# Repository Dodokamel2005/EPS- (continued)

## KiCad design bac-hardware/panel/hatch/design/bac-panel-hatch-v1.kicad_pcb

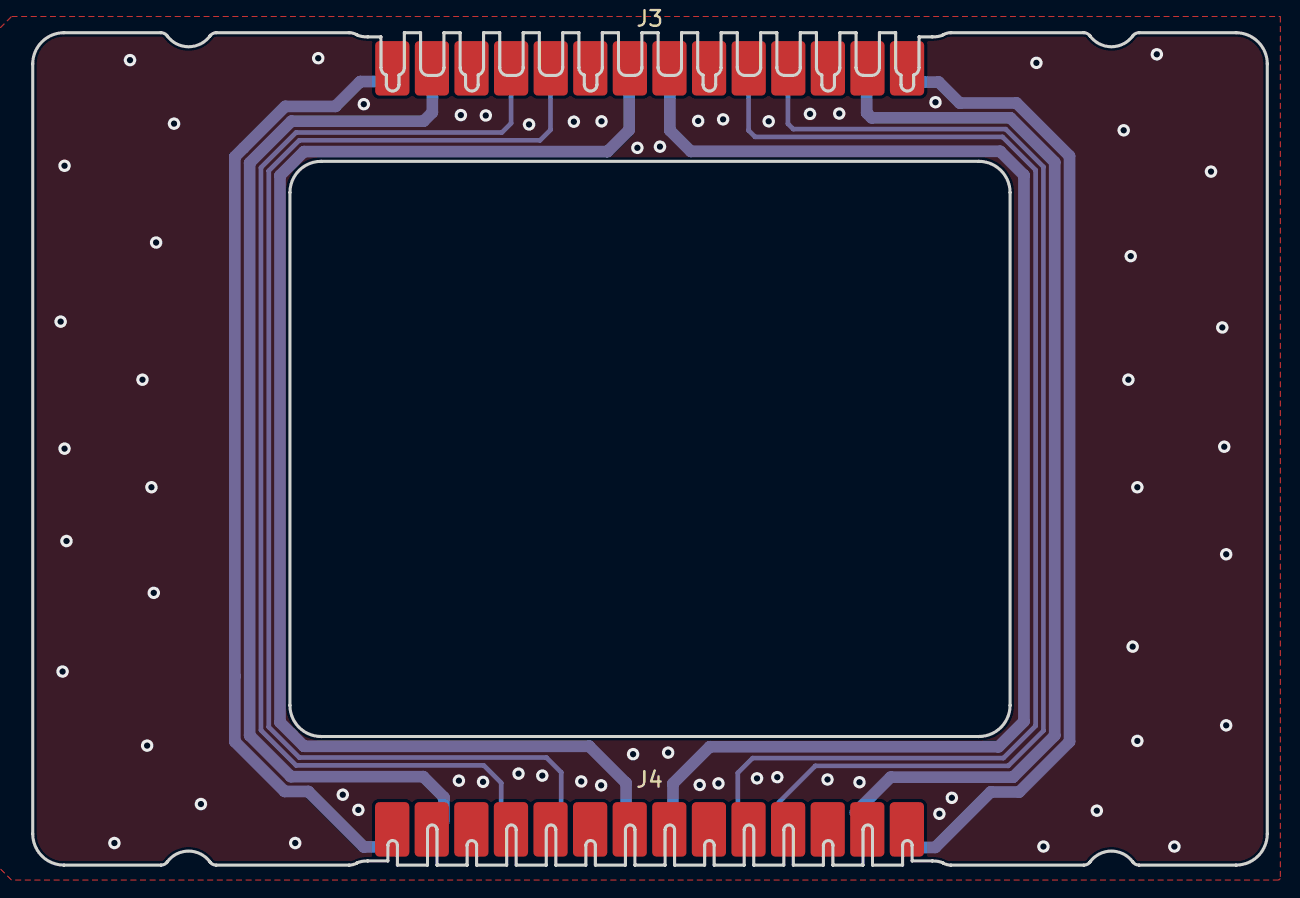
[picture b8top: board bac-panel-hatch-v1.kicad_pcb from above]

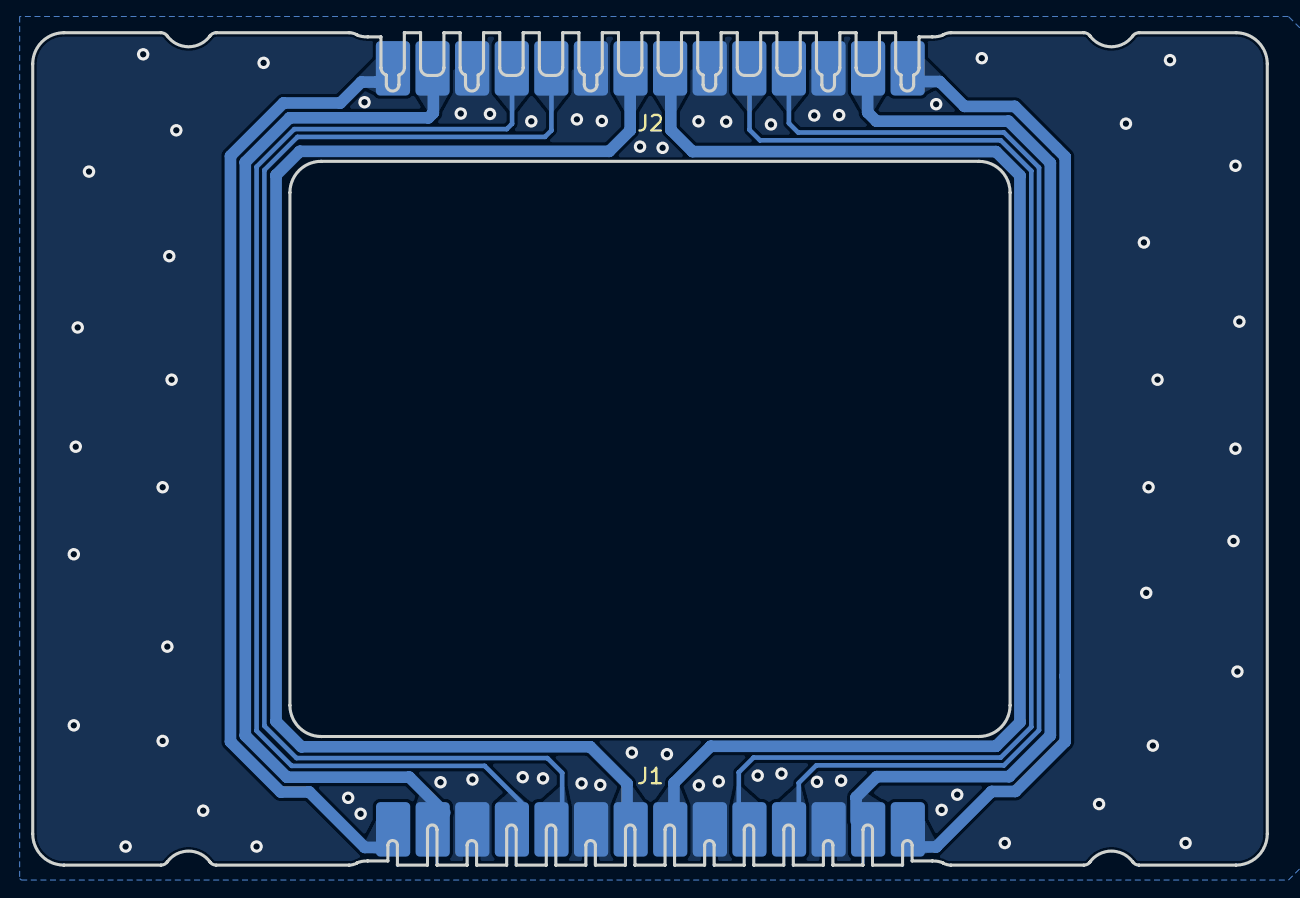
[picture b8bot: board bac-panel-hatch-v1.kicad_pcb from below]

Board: 2 copper layers, 79.2 x 53.4 mm, 4 parts (2 on the bottom side), 11 nets.

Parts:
J1, J2, J3, J4: Panel Connector 1x16; bac-panel-v1-14P-pad-row

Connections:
/3v3_A: J1.7, J2.7
/3v3_B: J1.8, J2.8
/DEPLOY_2/RBF: J1.1, J2.1
/EN_PANEL_B: J1.14, J2.14
/PANEL_SCL_A: J1.4, J2.4
/PANEL_SCL_B: J1.11, J2.11
/PANEL_SDA_A: J1.5, J2.5
/PANEL_SDA_B: J1.10, J2.10
/VPV_A: J1.2, J2.2
/VPV_B: J1.13, J2.13
GND: J1.3, J1.6, J1.9, J1.12, J2.3, J2.6, J2.9, J2.12

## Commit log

2025-06-11 Battery charge controller
2025-06-12 EPS version 1
